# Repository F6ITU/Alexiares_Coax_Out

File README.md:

# Alexiares_Coax_Out V2

Kicad files

OpenHPSDR RX and TX rear panel crowbar (coax input and output)

###Version 2.0

This version includes the "Pure Signal" relay input comming from inside or outside of the rig
 
This relay forwards PS_in or hpf out to the default RX or ADC depending on the state of 

TX_RX_Relay signal

for more informations, please refer to 

https://wiki.electrolab.fr/Projets:Lab:2017:Peripheriques_Angelia

This board could be cut in half and shielded

Input are fully compatible with Alexiares/Alexandrie output
TX antenna relays are rated at 150 W PEP (300 W maximum)

It also could work with DC2PD I2C interface 
and the forked version AlexI2C

3D image of the board are stored on this repo

RX_Ant dwn.jpg

RX_Ant_up.jpg

Bom is available in CSV format

Schematics, pcb design, modules and libs are in Kicad format

Gerber files are fully compatible with Protel 4.6 format

Board's dimensions are oversized to fit the 5x10 and 10x10cm size of all board of the Hermes project under Kicad:

* Alexandrie (Ἀλεξάνδρεια), Alexiares SPI interface
* Alexi2C ( Ἄλεξις), Alternate Alexiares I2C interface
* Alexiares_lpf (Ἀλεξιάρης) Alexiares low pass filter
* Alexiares_hpf (Ἀλεξιάρης) Alexiares high-pass filter
* Alexiares_Coax_Out (Ἀλεξιάρης ) Alexiares antenna switch boards
* Télémaque (Τηλέμαχος),  SSPA U/V/C°/Refl/FWD sensor for the Mentor board 
* Mentor (Μέντωρ) Micro-controler unit(MCU) and security module controling Telemaque informations
* Ulysse ou Odysseus (Ὀδυσσεύς), medium power reflectometer for the Telemaque/Mentor set
* Themis (Θέμις), low power bidirectionnal reflectometer with pre-distorsion (pure signal) output
* Aiôn (αἰών), 10 MHz low drift, low phase noise clock (general purpose)
* Hébé (Ἥβη), EER control system for high efficiency power amp

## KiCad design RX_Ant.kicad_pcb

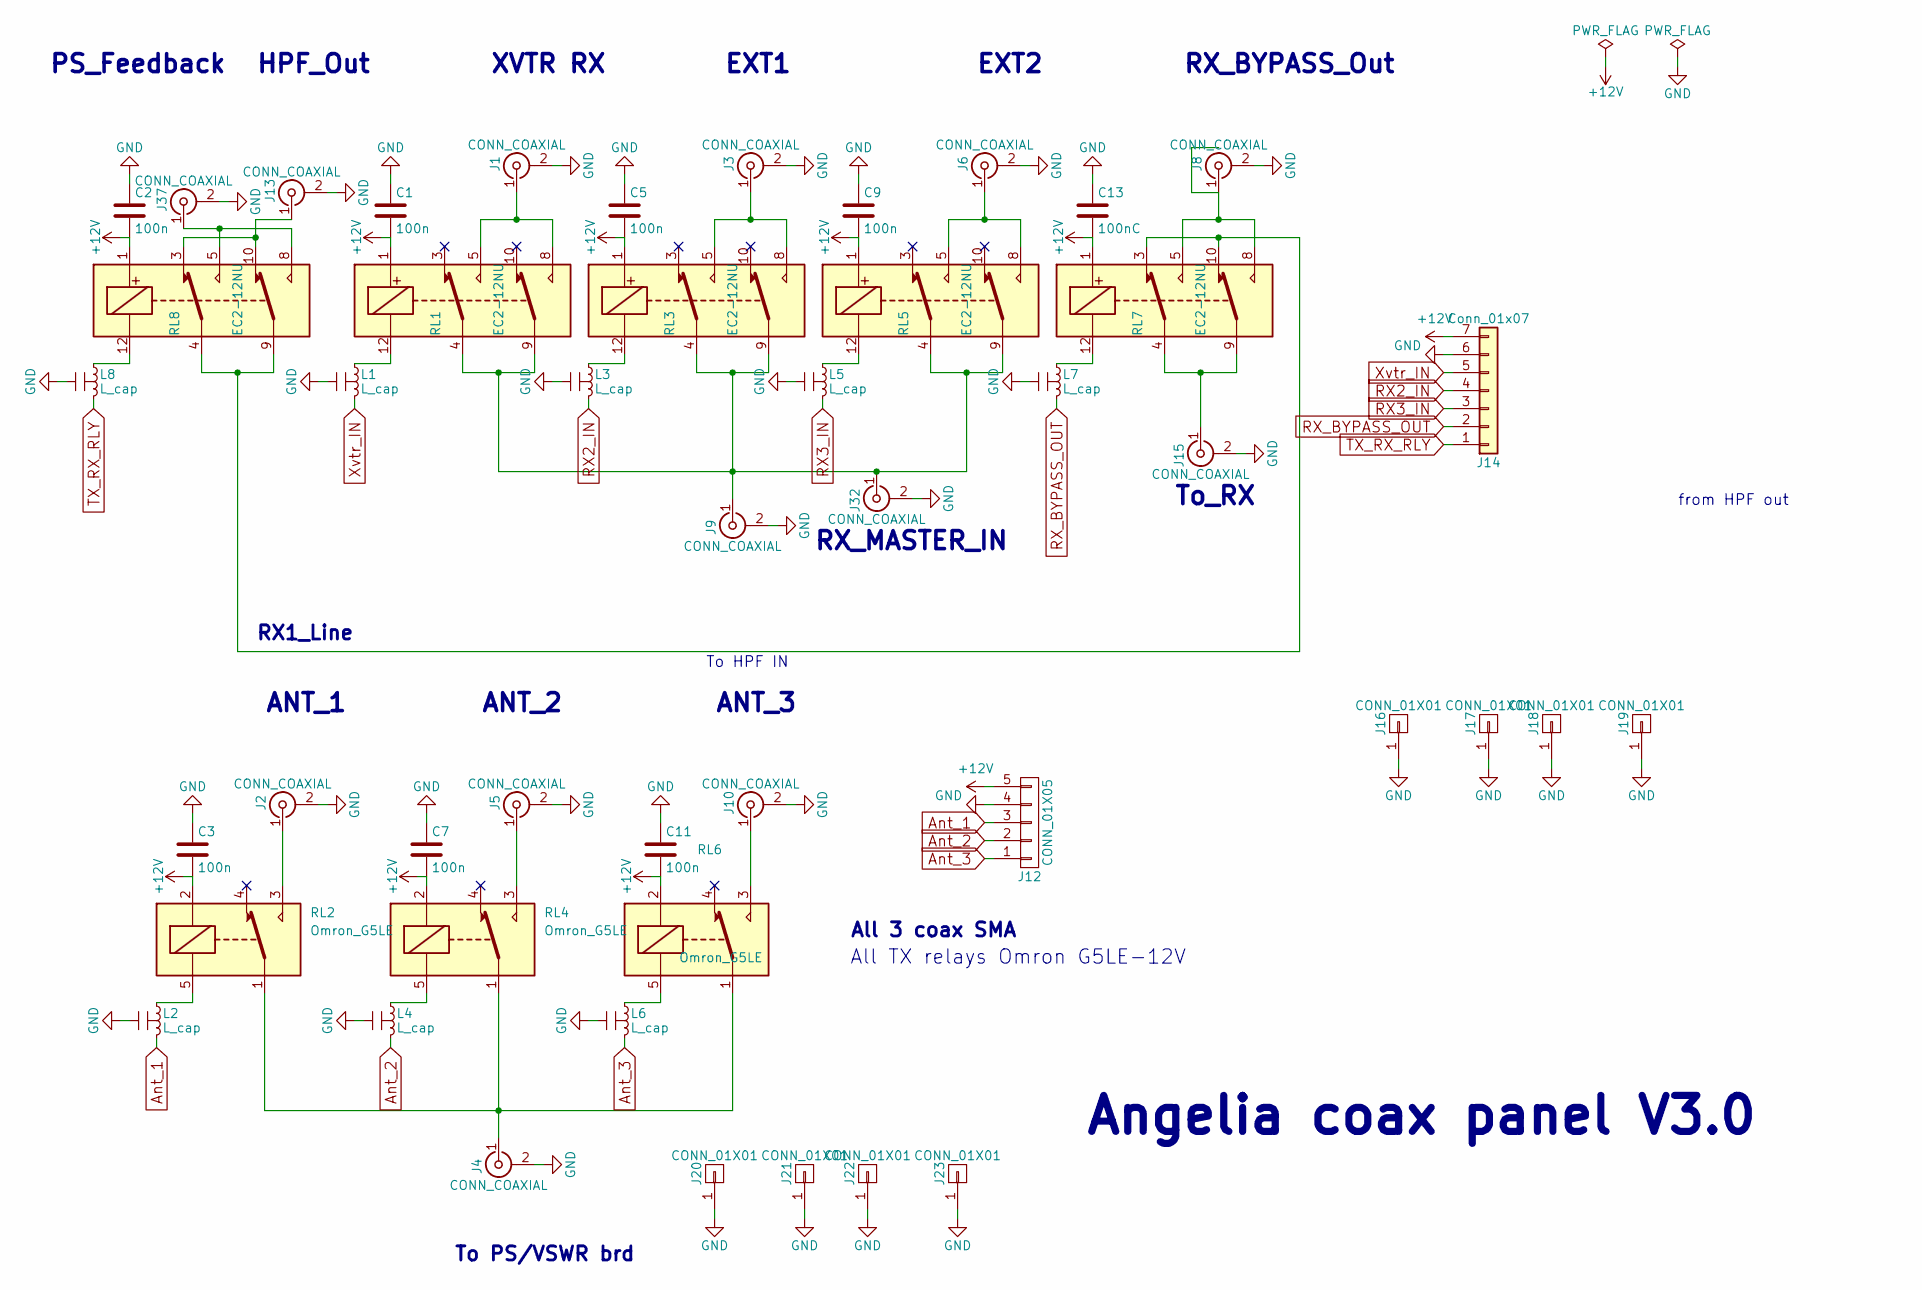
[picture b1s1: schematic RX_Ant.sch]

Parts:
C1, C2, C3, C5, C7, C9, C11: 100n; C_0805_HandSoldering
C13: 100nC; C_0805_HandSoldering
J1, J2, J3, J4, J5, J6, J8, J9, J10, J13, J15, J32, J37: CONN_COAXIAL; sma_straight_32k101-400l5
J12: CONN_01X05; kk100_22-23-2051
J14: Conn_01x07; Molex_KK-6410-07_07x2.54mm_Straight
J16, J17, J18, J19, J20, J21, J22, J23: CONN_01X01; MountingHole_3.5mm_Pad
L1, L2, L3, L4, L5, L6, L7, L8: L_cap; Ferrite_LC_NFM41P
RL1, RL3, RL5, RL7, RL8: EC2-12NU; THT_2_formC
RL2, RL4, RL6: Omron_G5LE

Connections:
+12V: C1.2, C2.2, C3.2, C5.2, C7.2, C9.2, C11.2, C13.2, J12.5, J14.7, RL1.1, RL2.2, RL3.1, RL4.2, RL5.1, RL6.2, RL7.1, RL8.1
Ant_1: J12.3, L2.3
Ant_2: J12.2, L4.3
Ant_3: J12.1, L6.3
GND: C1.1, C2.1, C3.1, C5.1, C7.1, C9.1, C11.1, C13.1, J1.2 (Ext), J2.2 (Ext), J3.2 (Ext), J4.2 (Ext), J5.2 (Ext), J6.2 (Ext), J8.2 (Ext), J9.2 (Ext), J10.2 (Ext), J12.4, J13.2 (Ext), J14.6, J15.2 (Ext), J16.1, J17.1, J18.1, J19.1, J20.1, J21.1, J22.1, J23.1, J32.2 (Ext), J37.2 (Ext), L1.2, L2.2, L3.2, L4.2, L5.2, L6.2, L7.2, L8.2
unnamed: J1.1 (In), RL1.5, RL1.8
unnamed: J2.1 (In), RL2.3
unnamed: J3.1 (In), RL3.5, RL3.8
unnamed: J4.1 (In), RL2.1, RL4.1, RL6.1
unnamed: J5.1 (In), RL4.3
unnamed: J6.1 (In), RL5.5, RL5.8
unnamed: J8.1 (In), RL7.5, RL7.8
unnamed: J10.1 (In), RL6.3
unnamed: J13.1 (In), RL8.3, RL8.10
unnamed: J15.1 (In), RL7.4, RL7.9
unnamed: J9.1 (In), J32.1 (In), RL1.4, RL1.9, RL3.4, RL3.9, RL5.4, RL5.9
unnamed: J37.1 (In), RL8.5, RL8.8
unnamed: L1.1, RL1.12
unnamed: L2.1, RL2.5
unnamed: L3.1, RL3.12
unnamed: L4.1, RL4.5
unnamed: L5.1, RL5.12
unnamed: L6.1, RL6.5
unnamed: L7.1, RL7.12
unnamed: L8.1, RL8.12
unnamed: RL7.3, RL7.10, RL8.4, RL8.9
RX2_IN: J14.4, L3.3
RX3_IN: J14.3, L5.3
RX_BYPASS_OUT: J14.2, L7.3
TX_RX_RLY: J14.1, L8.3
Xvtr_IN: J14.5, L1.3

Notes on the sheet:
ANT_1
ANT_2
ANT_3
To PS/VSWR brd
XVTR RX
EXT2
EXT1
RX_BYPASS_Out
To_RX
To HPF IN
Angelia coax panel V3.0
All 3 coax SMA
from HPF out
RX_MASTER_IN
All TX relays Omron G5LE-12V
PS_Feedback
RX1_Line
HPF_Out

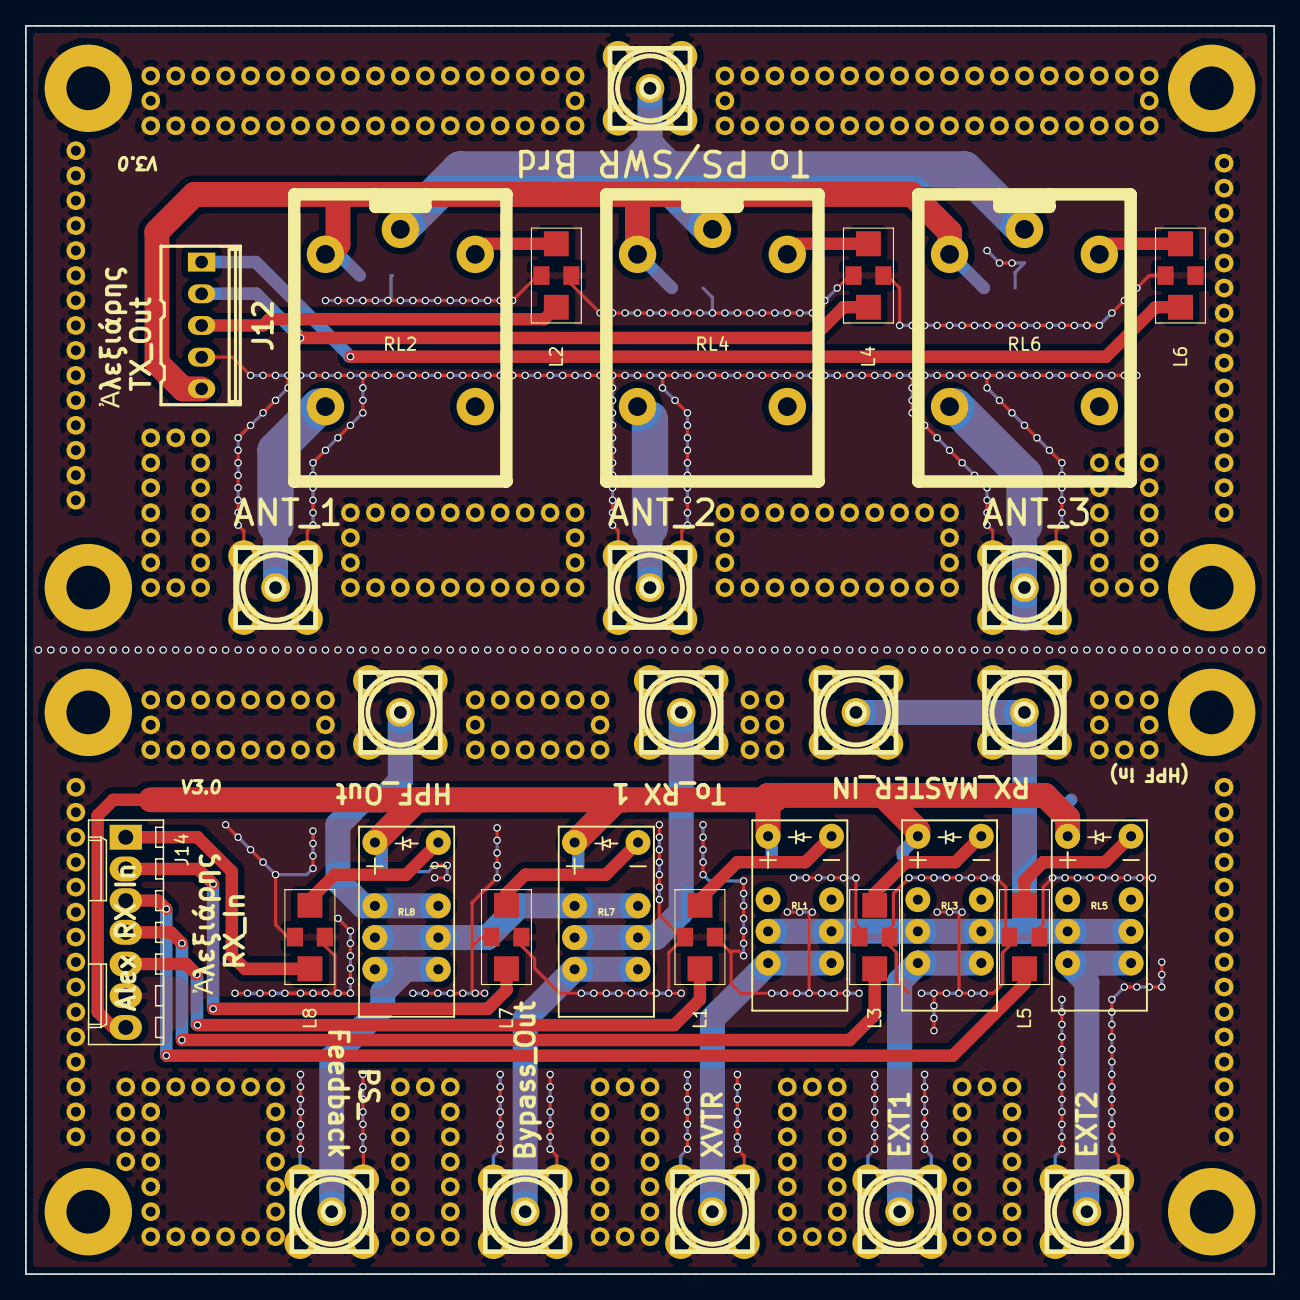
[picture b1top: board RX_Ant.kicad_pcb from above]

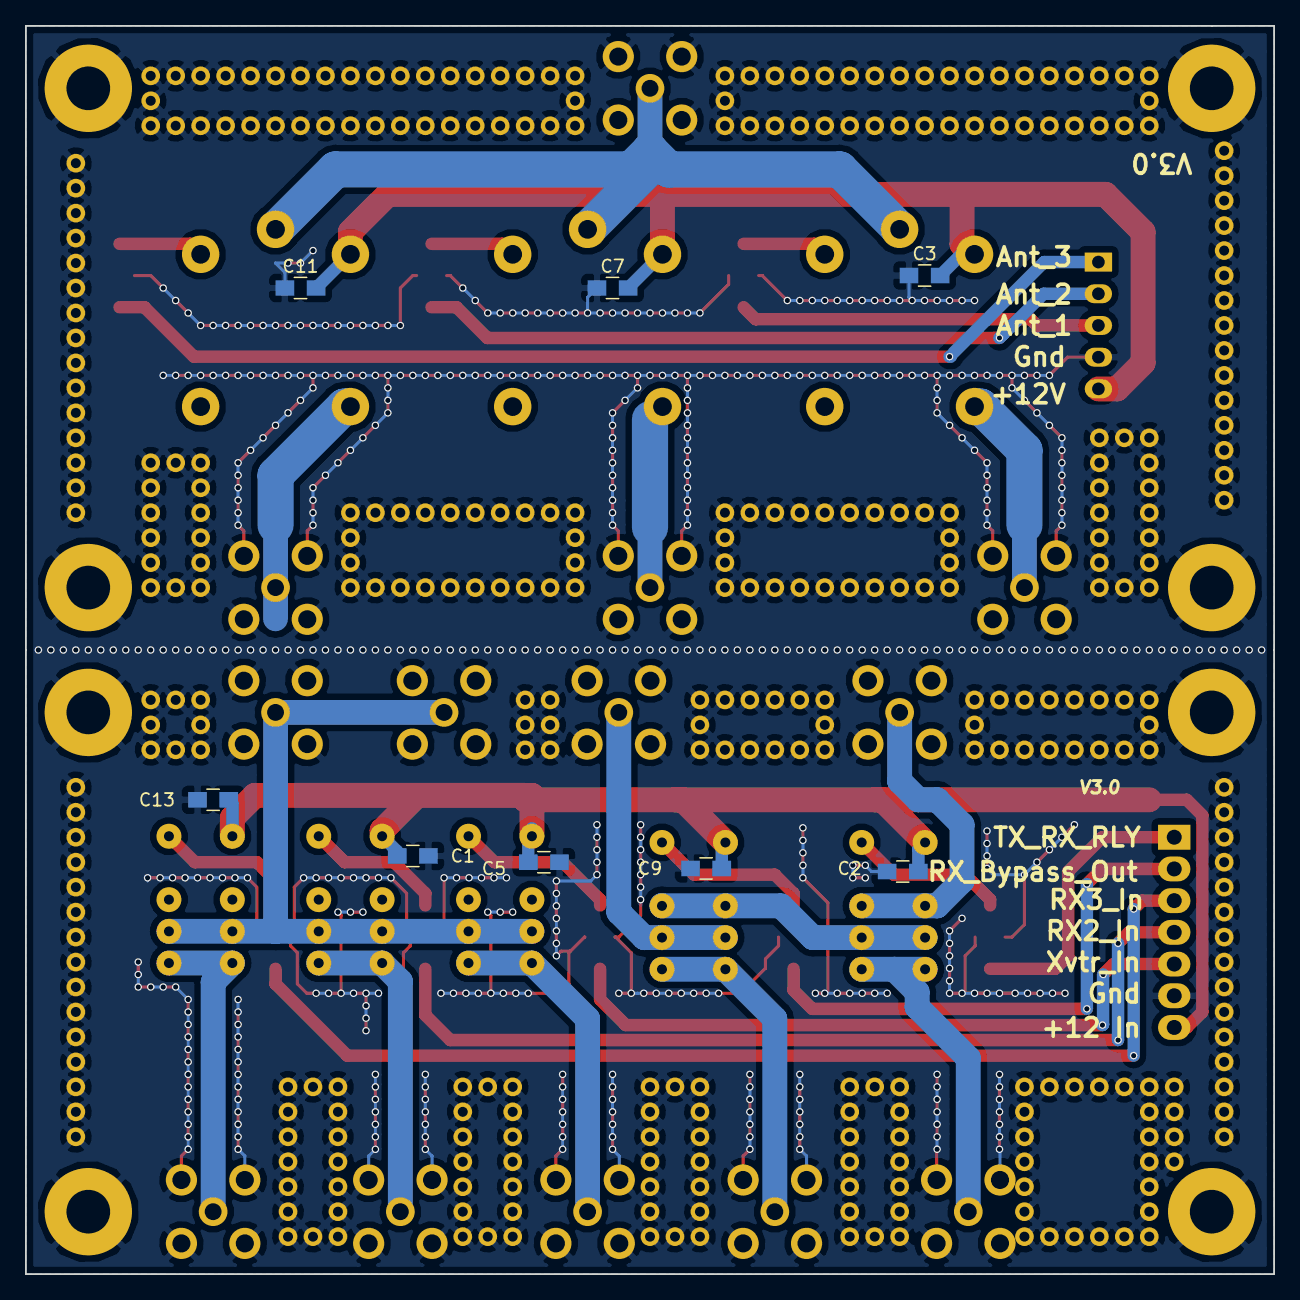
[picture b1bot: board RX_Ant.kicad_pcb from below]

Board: 2 copper layers, 100.0 x 100.0 mm, 47 parts (8 on the bottom side), 31 nets.

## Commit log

2017-06-12 1st schematic drawing compatible w. Alex V. 24
2017-10-03 adding sma and relay modules
2017-11-01 RTM 1
2017-11-02 silk and gnd error fixed
2017-11-02 Readme cleaning, add 2 3D pictures
2017-11-02 Readme cleanup
2017-11-27 few more vias added, tidying up some silkmask
2017-12-30 Gerber and BOM files added
2017-12-30 component values added, BOM changed
2018-01-05 via stitching added, new gerber
2018-01-05 via stitching, gerber added
2018-01-06 new routing, new gerber
2018-01-07 stiching again, new gerber
2018-01-21 creation branche V1, stable, modif SMA
2018-01-21 new readme, new 3D pics
2018-01-21 test modif readme sur branch master
2018-01-21 PS_In relay added, new routing V2
2018-01-21 new bom, new picture, new design, new stitching
2018-01-21 new readme
2018-02-25 minor fix, SMA edge must be changed
2018-02-25 added V1 marker on silk
2018-02-25 minor errors fixed, sma edge should be changed
2018-06-05 V3.0, RX_master connector added, new stitching
2018-06-05 gerber added
2019-03-15 upgrate to Kicad 5.0n, new up to date Gerber
